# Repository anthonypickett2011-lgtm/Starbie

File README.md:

#Starbie
a small tamogachi like PCB pet that can perceive its enviornment and be interacted with

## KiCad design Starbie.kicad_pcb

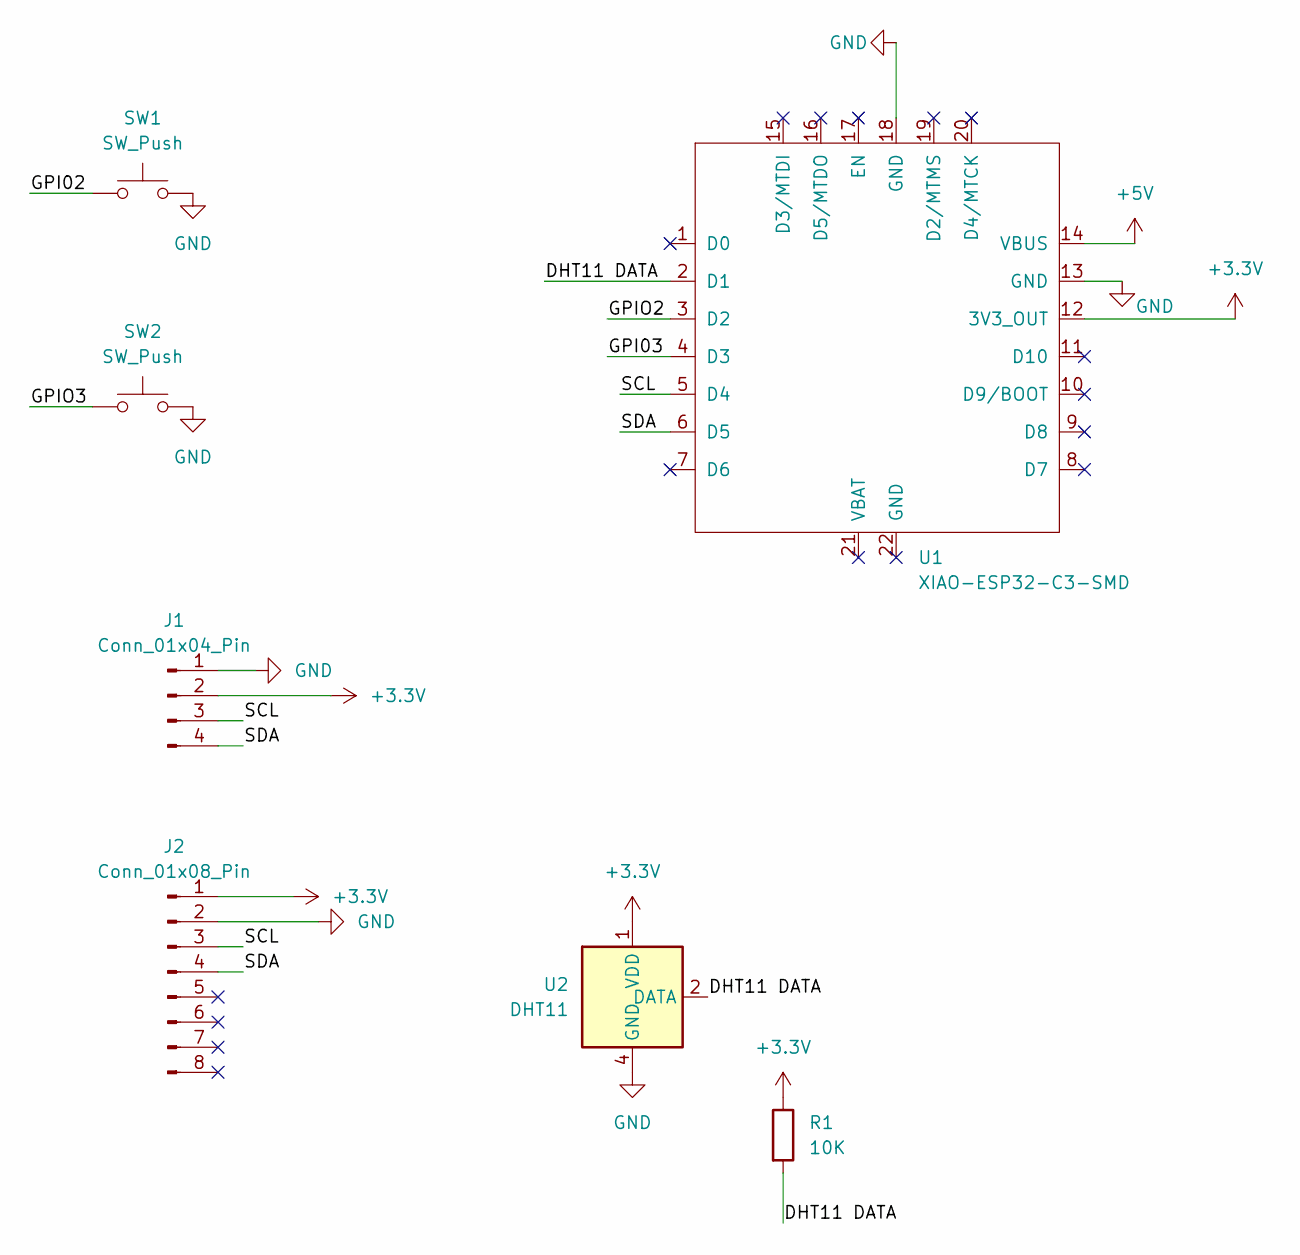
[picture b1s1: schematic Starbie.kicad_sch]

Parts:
J1: Conn_01x04_Pin; Display_128x64_096_I2C
J2: Conn_01x08_Pin; PinHeader_1x08_P2.54mm_Vertical
R1: 10K; R_Axial_DIN0204_L3.6mm_D1.6mm_P7.62mm_Horizontal
SW1, SW2: SW_Push; SW_Cherry_MX_1.00u_PCB
U1: XIAO-ESP32-C3-SMD
U2: DHT11; Aosong_DHT11_5.5x12.0_P2.54mm

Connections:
+3.3V: J1.2, J2.1, R1.1, U1.12 (3V3_OUT), U2.1 (VDD)
+5V: U1.14 (VBUS)
/DHT11 DATA: R1.2, U1.2 (D1), U2.2 (DATA)
/GPI02: SW1.1
/GPI03: U1.4 (D3)
/GPIO2: U1.3 (D2)
/GPIO3: SW2.1
/SCL: J1.3, J2.3, U1.5 (D4)
/SDA: J1.4, J2.4, U1.6 (D5)
GND: J1.1, J2.2, SW1.2, SW2.2, U1.13 (GND), U1.18 (GND), U2.4 (GND)

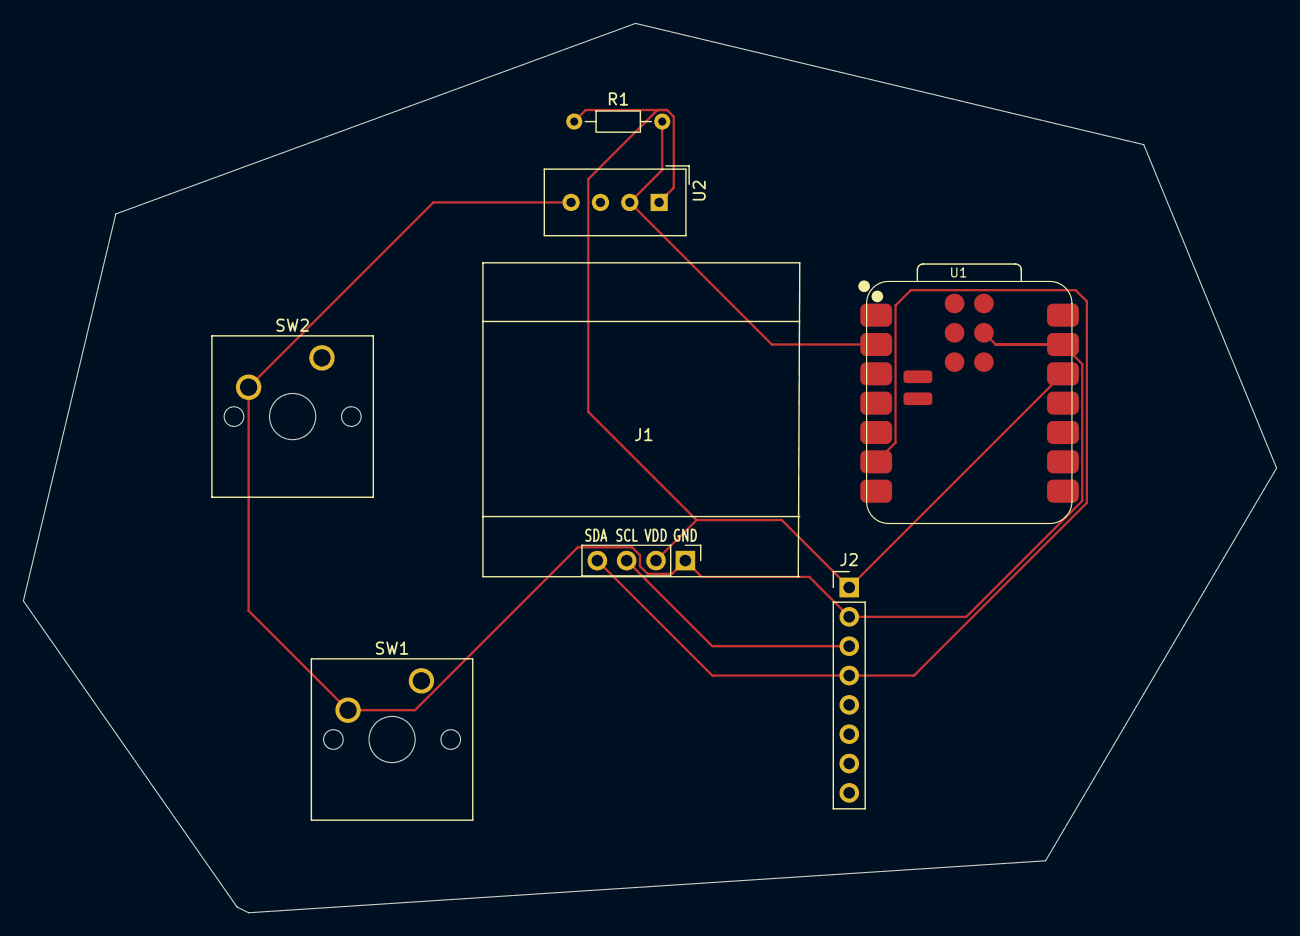
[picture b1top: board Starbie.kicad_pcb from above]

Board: 2 copper layers, 108.5 x 77.0 mm, 7 parts (0 on the bottom side), 5 nets.
